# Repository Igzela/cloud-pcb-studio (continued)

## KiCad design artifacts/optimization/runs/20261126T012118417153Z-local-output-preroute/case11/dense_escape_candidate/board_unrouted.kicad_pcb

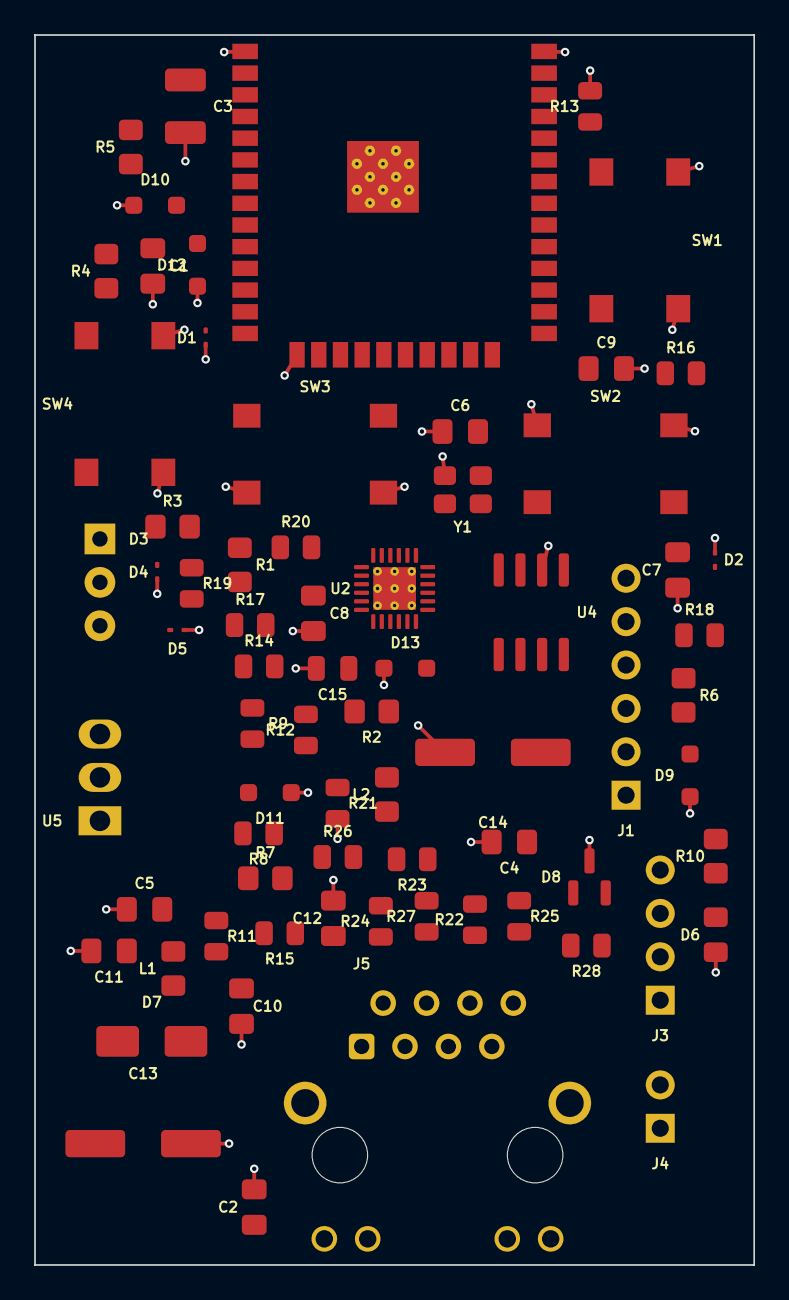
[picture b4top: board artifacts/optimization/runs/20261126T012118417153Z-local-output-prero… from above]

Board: 4 copper layers, 42.1 x 72.0 mm, 71 parts (0 on the bottom side), 49 nets.

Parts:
C1, C4: 1u; C_0805_2012Metric_Pad1.18x1.45mm_HandSolder
C2: 10u; C_0805_2012Metric_Pad1.18x1.45mm_HandSolder
C3: 100u; CP_EIA-3528-21_Kemet-B
C5, C7, C10, C11: 100n; C_0805_2012Metric_Pad1.18x1.45mm_HandSolder
C6, C8: 1uF; C_0805_2012Metric_Pad1.18x1.45mm_HandSolder
C9: 470pF; C_0805_2012Metric_Pad1.18x1.45mm_HandSolder
C12: 22nF; C_0805_2012Metric_Pad1.18x1.45mm_HandSolder
C13: 10uF; CP_Elec_6.3x4.9
C14: 1uF; CP_Elec_6.3x4.9
C15: 100nF; C_0805_2012Metric
D1, D2, D4, D5: ESD9B3; D_SOD-923
D3: LED_Dual_KAK; LED_D5.0mm-3
D6: LED; LED_0805_2012Metric_Pad1.15x1.40mm_HandSolder
D7: 1N5819; D_SMA
D8: NUP2105L; SOT-23
D9, D10, D11, D12, D13: PESD3V3L1BA; D_SOD-323_HandSoldering
J1: PROG; PinHeader_1x06_P2.54mm_Vertical
J3: Conn_Left_I2C; PinHeader_1x04_P2.54mm_Vertical
J4: Conn_01x02; PinHeader_1x02_P2.54mm_Vertical
J5: RJ45_Hanrun_HR911105A_Horizontal
L1, L2: BLM21SP181SN1D; R_0805_2012Metric_Pad1.20x1.40mm_HandSolder
R1, R2, R5, R6: 10k; R_0805_2012Metric_Pad1.20x1.40mm_HandSolder
R3, R4: 270R; R_0805_2012Metric_Pad1.20x1.40mm_HandSolder
R7: 0R; R_0805_2012Metric_Pad1.20x1.40mm_HandSolder
R8, R9: 10K; R_0805_2012Metric
R10: 470R; R_0805_2012Metric_Pad1.20x1.40mm_HandSolder
R11, R16, R18, R20: 33R; R_0805_2012Metric
R12: 1K5; R_0805_2012Metric
R13: 4K7; R_0805_2012Metric
R14, R15, R17, R19: 10R; R_0805_2012Metric
R21: 12K1; R_0805_2012Metric
R22, R23, R24, R27: 49R9; R_0805_2012Metric
R25, R26: 270R; R_0805_2012Metric
R28: 120R; R_0805_2012Metric
SW1: RESET; SW_SPST_Omron_B3FS-100xP
SW2: BOOT; SW_SPST_Omron_B3FS-100xP
SW3: Control 1; SW_SPST_Omron_B3FS-100xP
SW4: Control 2; SW_SPST_Omron_B3FS-100xP
U1: ESP32-WROOM-32
U2: LAN8720A; VQFN-24-1EP_4x4mm_P0.5mm_EP2.5x2.5mm_ThermalVias
U4: SN65HVD232; SOIC-8_3.9x4.9mm_P1.27mm
U5: R-78B3.3-2.0; Converter_DCDC_RECOM_R-78B-2.0_THT
Y1: 50MHz; Oscillator_SMD_Abracon_ASE-4Pin_3.2x2.5mm

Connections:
+3.3V: C2.1, C3.1, C6.2, C7.2, C8.1, C9.1, C14.1, C15.1, D13.2 (A2), J1.6, J5.9, J5.12, L1.2, L2.2, R1.2, R2.2, R5.2, R6.2, R7.2, R8.1, R9.1, R10.2, R11.1, R12.1, R15.1, U1.2 (VDD), U2.6 (VDDCR), U2.9 (VDDIO), U4.3 (VCC), U5.3 (OUT), Y1.4 (Vdd)
+24V: D7.2 (A), J3.1
/CAN/CANH: D8.2 (K), J3.2, J4.2, U4.7 (CANH)
/CAN/CANL: D8.1 (K), J3.3, R28.2, U4.6 (CANL)
/CPU/EN: C1.1, D1.2 (A2), D12.2 (A2), J1.5, R1.1, R5.1, SW1.2, U1.3 (EN)
/CPU/LEDA: R4.2, U1.6 (IO34)
/CPU/LEDB: R3.2, U1.7 (IO35)
/CPU/RX: J1.2, U1.34 (RXD0/IO3)
/CPU/TX: J1.3, U1.35 (TXD0/IO1)
/Ethernet/PHY_L1: R25.1, U2.3 (LED1/REGOFF)
/Ethernet/PHY_L2: R26.1, U2.2 (LED2/~INTSEL)
/Ethernet/PHY_RD+: J5.3 (RD+), R24.2, U2.23 (RXP)
/Ethernet/PHY_RD-: J5.6 (RD-), R27.2, U2.22 (RXN)
/Ethernet/PHY_TD+: J5.1 (TD+), R22.2, U2.21 (TXP)
/Ethernet/PHY_TD-: J5.2 (TD-), R23.2, U2.20 (TXN)
CTRL1: D4.2 (A2), D10.2 (A2), R8.2, SW3.1
CTRL2: D5.2 (A2), D11.2 (A2), R9.2, SW4.1
ETH_CRS_DV: R14.1, U1.12 (IO27)
ETH_EN_CLK: R13.1, U1.28 (IO17), Y1.1 (EN)
ETH_MDC: U1.37 (IO23), U2.13 (MDC)
ETH_MDIO: R12.2, U1.30 (IO18), U2.12 (MDIO)
ETH_RXCLK: C4.1, D2.2 (A2), D9.2 (A2), J1.4, R2.1, R6.1, R16.1, R18.1, SW2.2, U1.25 (IO0)
ETH_RXD0: R19.1, U1.10 (IO25)
ETH_RXD1: R17.1, U1.11 (IO26)
ETH_TXD0: U1.31 (IO19), U2.17 (TXD0)
ETH_TXD1: U1.36 (IO22), U2.18 (TXD1)
ETH_TXEN: U1.33 (IO21), U2.16 (TXEN)
GND: C1.2, C2.2, C3.2, C4.2, C5.1, C6.1, C7.1, C8.2, C9.2, C10.2, C11.2, C12.2, C13.2, C14.2, C15.2, D1.1 (A1), D2.1 (A1), D4.1 (A1), D5.1 (A1), D6.1 (K), D8.3 (A), D9.1 (A1), D10.1 (A1), D11.1 (A1), D12.1 (A1), D13.1 (A1), J1.1, J3.4, J5.8, J5.SH, R13.2, R21.2, SW1.1, SW2.1, SW3.2, SW4.2, U1.1 (GND), U1.15 (GND), U1.38 (GND), U1.39 (GND), U2.25 (VSS), U4.2 (GND), U5.2 (GND), Y1.2 (GND)
unnamed: D3.2 (A), R7.1
unnamed: D3.1 (K1), R4.1
unnamed: D3.3 (K2), R3.1
unnamed: D6.2 (A), R10.1
unnamed: C13.1, D7.1 (K), U5.1 (IN)
unnamed: J4.1, R28.1
unnamed: J5.10, R26.2
unnamed: J5.11, R25.2
unnamed: C12.1, J5.4 (TCT), J5.5 (RCT), L2.1, R22.1, R23.1, R24.1, R27.1
unnamed: R14.2, U2.11 (CRS_DV/MODE2)
unnamed: R21.1, U2.24 (RBIAS)
unnamed: R19.2, U2.8 (RXD0/MODE0)
unnamed: R17.2, U2.7 (RXD1/MODE1)
unnamed: R15.2, U2.10 (RXER/PHYAD0)
unnamed: C10.1, C11.1, L1.1, U2.1 (VDD2A), U2.19 (VDD1A)
unnamed: R20.1, U2.5 (XTAL1/CLKIN)
unnamed: R18.2, U2.14 (~INT/REFCLKO)
unnamed: R16.2, R20.2, Y1.3 (OUT)
PHY_RST: C5.2, R11.2, U2.15 (~RST)
RXCAN: U1.18 (SWP/SD3), U4.4 (R)
TXCAN: U1.17 (SHD/SD2), U4.1 (D)

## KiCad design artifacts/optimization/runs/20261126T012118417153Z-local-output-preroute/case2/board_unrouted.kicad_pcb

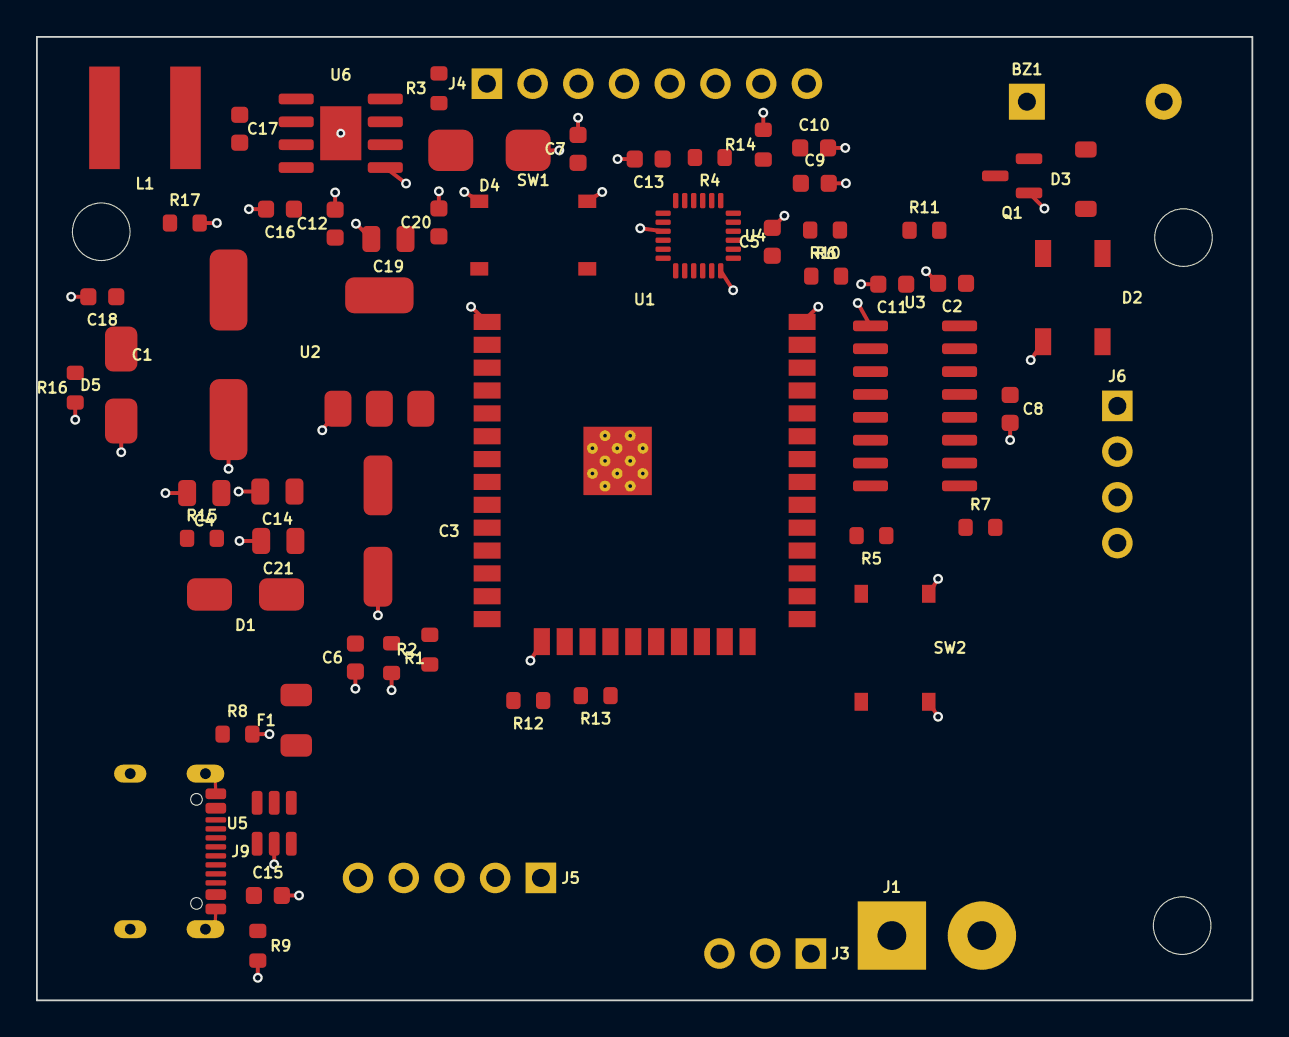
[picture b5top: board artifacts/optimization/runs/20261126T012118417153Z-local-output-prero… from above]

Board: 4 copper layers, 67.5 x 53.5 mm, 64 parts (0 on the bottom side), 50 nets.

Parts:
BZ1: Buzzer; Buzzer_12x9.5RM7.6
C1: 100uF 35V; C_Elec_8x10.2
C2, C5, C6, C7, C8, C9, C12, C13, C15, C16, C17, C20: 100nF; C_0603_1608Metric
C3: 100uF 16V; C_Elec_6.3x5.8
C4: 10uF 16V; C_0805_2012Metric
C10: 2.2nF; C_0603_1608Metric
C11: 10nF; C_0603_1608Metric
C14: 22uF; C_0805_2012Metric
C18: 220p; C_0603_1608Metric
C19, C21: 10uF; C_0805_2012Metric
D1: SS34; D_SMA
D2: WS2812B; LED_WS2812B_PLCC4_5.0x5.0mm_P3.2mm
D3: 1N4148; D_SOD-123
D4: SM6T24A; D_SMB
D5: D_Schottky; D_SMA
F1: 500mA; Fuse_1206_3216Metric
H1, H2, H3: M_3.2mm; MountingHole_3.2mm
J1: Battery XT30; AMASS_XT30U-M_1x02_P5.0mm_Vertical
J3: IBUS/SBUS RECIEVER; PinHeader_1x03_P2.54mm_Vertical
J4: PWM RECIEVER; PinHeader_1x08_P2.54mm_Vertical
J5: MOTOR OUT; PinHeader_1x05_P2.54mm_Vertical
J6: GPS; PinHeader_1x04_P2.54mm_Vertical
J9: USB_C_Receptacle_USB2.0_16P; USB_C_Receptacle_GCT_USB4105-xx-A_16P_TopMnt_Horizontal
L1: 22u; L_Sunlord_SWPA6028S
Q1: 2N3904; SOT-23
R1: 22k; R_0603_1608Metric
R2, R3: 100k; R_0603_1608Metric
R4, R5: 10k; R_0603_1608Metric
R6: 1k; R_0603_1608Metric
R7: 330k; R_0603_1608Metric
R8, R9: 5.1k; R_0603_1608Metric
R10, R11: 4.7k; R_0603_1608Metric
R12, R13: 22; R_0603_1608Metric
R14: 200k; R_0603_1608Metric
R15: 211k; R_0603_1608Metric
R16: 40.2k; R_0603_1608Metric
R17: 68.1k; R_0603_1608Metric
SW1: RESET; SW_Push_1P1T_XKB_TS-1187A
SW2: BOOT; SW_Push_1P1T_XKB_TS-1187A
U1: ESP32-WROOM-32E; ESP32-WROOM-32D
U2: AMS1117-3.3; SOT-223-3_TabPin2
U3: CH340C; SOIC-16_3.9x9.9mm_P1.27mm
U4: MPU-6050; InvenSense_QFN-24_4x4mm_P0.5mm
U5: USBLC6-2SC6; SOT-23-6
U6: MP1584EN; SOIC-8-1EP_3.9x4.9mm_P1.27mm_EP2.29x3mm

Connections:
+3.3V: C2.1, C4.1, C5.1, C7.1, C11.1, C12.1, C13.1, J6.1, R4.1, R5.1, R10.1, R11.1, U1.2, U2.2, U3.16, U4.8, U4.13
+3V3: BZ1.2, D2.1, D3.1
+5V: C3.1, C14.1, C19.1, C20.1, C21.1, F1.2, J3.2, J4.7, L1.1, R15.2, U2.3
+BATT: D1.2, J1.1, R2.1
/VIN: C1.2, C16.1, D1.1, D4.2, R3.1, U6.7
/usb+: J9.A6, J9.B6, U5.1
/usb-: J9.A7, J9.B7, U5.3
/usb_esd-: R13.2, U5.4
/usb_mcu+: R12.1, U3.5
/usb_mcu-: R13.1, U3.6
BUZZER: R6.1, U1.16
CH1: J4.1, U1.8
CH2: J4.2, U1.9
CH3: J4.3, U1.7
CH4: J4.4, U1.30
CH5: J4.5, U1.31
CH6: J4.6, U1.37
ESC1: J5.1, U1.10
ESC2: J5.2, U1.11
ESC3: J5.3, U1.12
ESC4: J5.4, U1.13
GND: C1.1, C2.2, C3.2, C4.2, C5.2, C6.1, C7.2, C8.2, C9.2, C10.2, C11.2, C12.2, C13.2, C14.2, C15.2, C16.2, C18.2, C19.2, C20.2, C21.2, D2.3, D4.1, D5.1, J1.2, J3.3, J4.8, J5.5, J6.2, J9.A1, J9.A12, J9.B1, J9.B12, J9.S1, Q1.1, R1.2, R8.2, R9.2, R14.2, R16.1, R17.2, SW1.1, SW2.1, U1.1, U1.15, U1.38, U1.39, U2.1, U3.1, U4.9, U4.11, U4.18, U5.2, U6.5, U6.9
GPS RX: J6.4, U1.28
GPS TX: J6.3, U1.29
INT: U1.6, U4.12
LED_STAT: R7.1, U1.26
unnamed: BZ1.1, D3.2, Q1.2
unnamed: D2.4, R7.2
unnamed: C17.2, D5.2, L1.2, U6.1
unnamed: J9.A5, R8.1
unnamed: J9.B5, R9.1
unnamed: Q1.3, R6.2
unnamed: R12.2, U5.6
unnamed: R4.2, SW1.2, U1.3
unnamed: R5.2, SW2.2, U1.25
unnamed: C8.1, U3.4
unnamed: C10.1, U4.20
unnamed: C9.1, U4.10
unnamed: C15.1, F1.1, J9.A4, J9.A9, J9.B4, J9.B9, U5.5
unnamed: C17.1, U6.8
unnamed: C18.1, R17.1, U6.3
unnamed: R3.2, U6.2
unnamed: R15.1, R16.2, U6.4
unnamed: R14.1, U6.6
RX: U1.34, U3.2
SCL: R11.2, U1.36, U4.23
SDA: R10.2, U1.33, U4.24
SENOR_VP: C6.2, R1.1, R2.2, U1.4
TX: U1.35, U3.3
iBUS/SBUS RX: J3.1, U1.27

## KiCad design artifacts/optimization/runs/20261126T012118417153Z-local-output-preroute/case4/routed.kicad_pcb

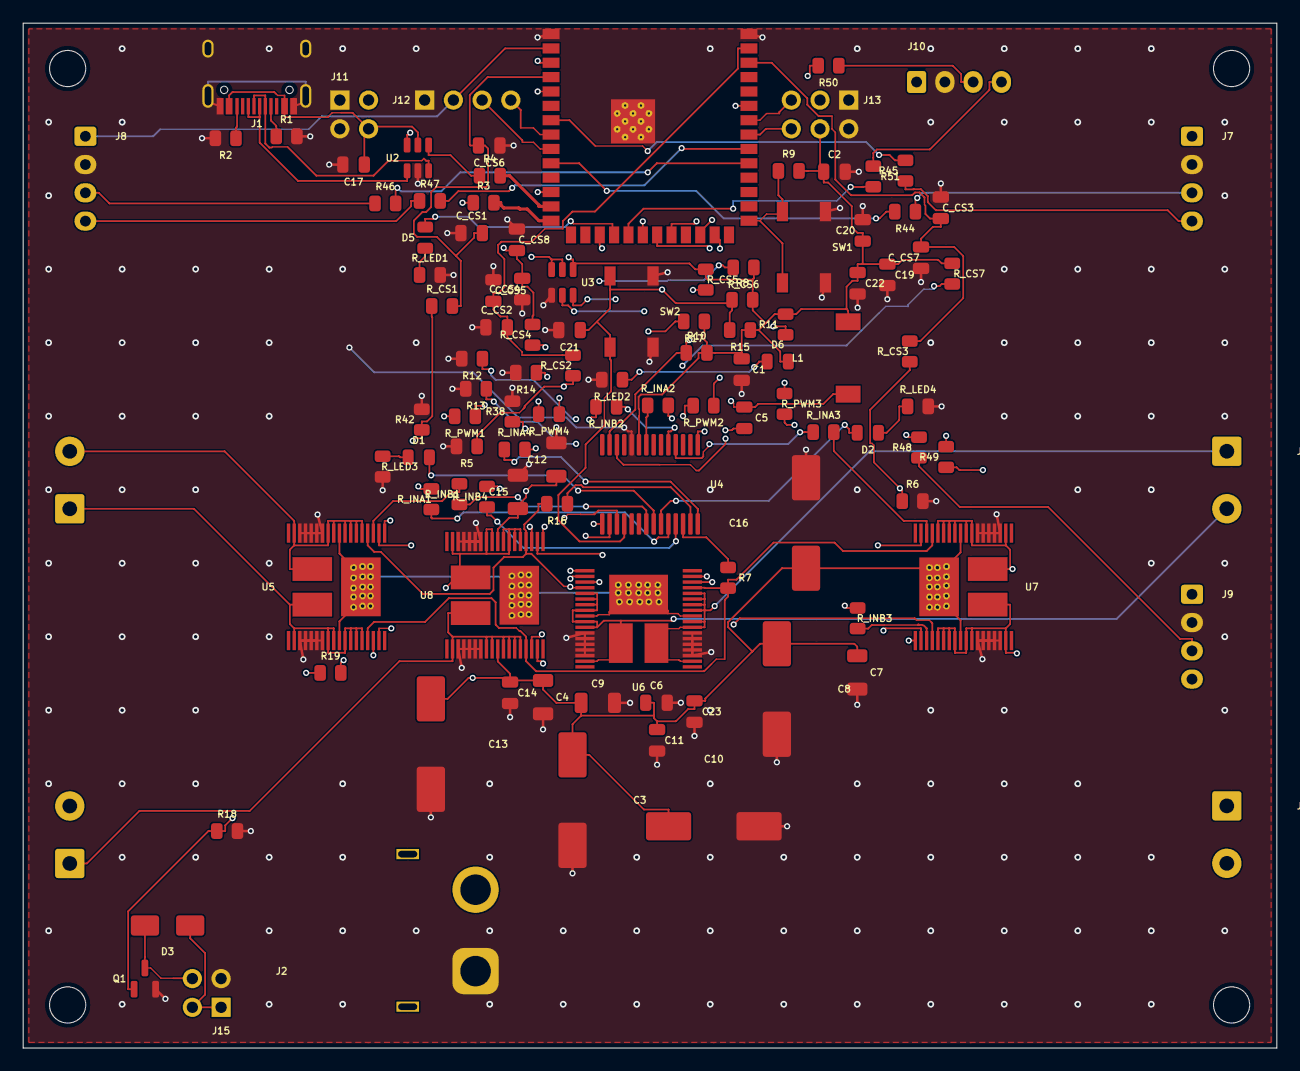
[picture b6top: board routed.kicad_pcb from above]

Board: 4 copper layers, 110.8 x 90.6 mm, 117 parts (0 on the bottom side), 98 nets.

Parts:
C1, C2: 22uF; C_0805_2012Metric
C3, C8, C10, C13, C16: 470uF; CP_Elec_10x10
C4, C7, C9, C12, C15: 10uF; C_1206_3216Metric
C5, C6, C11, C14, C19, C21, C22, C23: 100nF; C_0805_2012Metric
C17, C20: 10uF; C_0805_2012Metric
C_CS1, C_CS2, C_CS3, C_CS4: 100nF; C_0805_2012Metric
C_CS5, C_CS6, C_CS7, C_CS8: 10uF; C_0805_2012Metric
D1: Red LED; LED_0805_2012Metric
D2: Green LED; LED_0805_2012Metric
D3: D_Schottky; D_SMA
D5: Blue LED; LED_0805_2012Metric
D6: Orange LED; LED_0805_2012Metric
H1, H2, H3, H4: M_3.2mm; MountingHole_3.2mm
J1: USB_C_Receptacle_USB2.0_16P; USB_C_Receptacle_HRO_TYPE-C-31-M-12
J2: Conn_01x02; AMASS_XT60PW-M_1x02_P7.20mm_Horizontal
J3, J4, J5, J6: Conn_01x02; TerminalBlock_Phoenix_MKDS-3-2-5.08_1x02_P5.08mm_Horizontal
J7, J8, J9, J10: Conn_01x04; JST_XH_B4B-XH-A_1x04_P2.50mm_Vertical
J11: 5v breakout; PinHeader_2x02_P2.54mm_Vertical
J12: I2C sda scl; PinHeader_1x04_P2.54mm_Vertical
J13: 41(40)_3v3_gnd; PinHeader_2x03_P2.54mm_Vertical
J15: IN OUT; PinHeader_2x02_P2.54mm_Vertical
L1: 4.7uH; L_7.3x7.3_H4.5
Q1: Q_NMOS_GDS; SOT-23
R1, R2: 5.1K; R_0805_2012Metric
R3, R4: 27R; R_0805_2012Metric
R5, R6, R17, R38, R42: 1K; R_0805_2012Metric
R7, R16: 1k; R_0805_2012Metric
R8, R9, R12, R13, R14, R15: 10K; R_0805_2012Metric
R10, R11: 4.7K; R_0805_2012Metric
R18: 10k; R_0805_2012Metric
R19, R44, R45, R46, R47, R48, R49, R50, R51: 100R; R_0805_2012Metric
R_CS1, R_CS2, R_CS3, R_CS4, R_CS5, R_CS6, R_CS7: 1k; R_0805_2012Metric
R_INA1, R_INA2, R_INA3, R_INA4: 1K; R_0805_2012Metric
R_INB1, R_INB2, R_INB3, R_INB4: 1K; R_0805_2012Metric
R_LED1, R_LED2, R_LED3, R_LED4: 330R; R_0805_2012Metric
R_PWM1, R_PWM2, R_PWM3, R_PWM4: 1K; R_0805_2012Metric
SW1: SW_Boot; SW_SPST_TL3342
SW2: SW_RESET; SW_SPST_TL3342
U1: ESP32-S3-WROOM-1
U2: USBLC6-2SC6; SOT-23-6
U3: AP63203WU-7; TSOT-23-6-AP63203WU
U4: MCP23017_SS; SSOP-28_5.3x10.2mm_P0.65mm
U5, U6, U7, U8: VNH7040AYTR; POWERSSO-36TP_STM_jr

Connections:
/3V3: C1.1, C2.1, C19.1, C20.1, C22.1, D6.2 (A), J7.1, J8.1, J9.1, J10.1, J12.2, J13.3, J13.4, L1.2, R8.2, R9.2, R10.2, R11.2, R15.1, R17.1, R_CS5.1, R_CS6.1, R_CS7.1, U1.2 (3V3), U3.1 (FB), U4.9 (VDD)
/3V3_M1: R_CS6.2, U5.20
/3V3_M2: R_CS7.2, U6.20
/3V3_m3: R_CS5.2, U7.20
/3v3_light: R17.2, U8.20
/5V_USB: C17.1, J1.A4 (VBUS), J1.A9 (VBUS), J1.B4 (VBUS), J1.B9 (VBUS), J11.2, J11.4, U2.5 (VBUS), U3.2 (EN), U3.3 (IN)
/ENCA_M1: R44.2, U1.10 (IO17)
/ENCA_M2: R46.2, U1.31 (IO38)
/ENCA_M3: R48.2, U1.22 (IO14)
/ENCA_M4: R50.2, U1.20 (IO12)
/ENCB_M1: R45.2, U1.7 (IO7)
/ENCB_M2: R47.2, U1.32 (IO39)
/ENCB_M3: R49.2, U1.24 (IO47)
/ENCB_M4: R51.2, U1.19 (IO11)
/ESP_EN: C21.1, R8.1, R15.2, SW2.2, U1.3 (EN), U4.18 (~RESET)
/GPIO40: J13.6, U1.33 (IO40)
/GPIO41: J13.5, U1.34 (IO41)
/Green_LED: D2.2 (A), U4.23 (GPA2)
/I2C_SCL: J12.4, R11.1, U1.8 (IO15), U4.12 (SCK)
/I2C_SDA: J12.3, R10.1, U1.9 (IO16), U4.13 (SDA)
/LED_ESP32: D5.2 (A), U1.18 (IO10)
/M1_CS: R42.1, R_CS1.1, U5.19
/M1_CS_ADC: C_CS1.2, C_CS6.2, R_CS1.2, U1.4 (IO4)
/M1_INA: R_INA1.2, U5.16
/M1_INA_ESP32: R_INA1.1, U4.24 (GPA3)
/M1_INB: R_INB1.2, U5.21
/M1_INB_ESP32: R_INB1.1, U4.21 (GPA0)
/M1_OUTA: J3.1, U5.2, U5.8, U5.9, U5.11, U5.12, U5.13, U5.14, U5.38
/M1_OUTB: J3.2, U5.23, U5.24, U5.25, U5.26, U5.28, U5.29, U5.35, U5.39
/M1_PWM: R_PWM1.2, U5.17
/M1_PWM_ESP: R_PWM1.1, U1.12 (IO8)
/M2_CS: R5.1, R_CS2.1, U6.19
/M2_CS_ADC: C_CS2.2, C_CS5.2, R_CS2.2, U1.39 (IO1)
/M2_INA: R_INA2.2, U6.16
/M2_INA_ESP32: R_INA2.1, U4.8 (GPB7)
/M2_INB: R_INB2.2, U6.21
/M2_INB_ESP32: R_INB2.1, U4.5 (GPB4)
/M2_OUTA: J4.1, U6.2, U6.8, U6.9, U6.11, U6.12, U6.13, U6.14, U6.38
/M2_OUTB: J4.2, U6.23, U6.24, U6.25, U6.26, U6.28, U6.29, U6.35, U6.39
/M2_PWM: R_PWM2.2, U6.17
/M2_PWM_ESP: R_PWM2.1, U1.25 (IO48)
/M3_CS: R6.1, R_CS3.1, U7.19
/M3_CS_ADC: C_CS3.2, C_CS7.2, R_CS3.2, U1.38 (IO2)
/M3_INA: R_INA3.2, U7.16
/M3_INA_ESP32: R_INA3.1, U4.4 (GPB3)
/M3_INB: R_INB3.2, U7.21
/M3_INB_ESP32: R_INB3.1, U4.1 (GPB0)
/M3_OUTA: J5.1, U7.2, U7.8, U7.9, U7.11, U7.12, U7.13, U7.14, U7.38
/M3_OUTB: J5.2, U7.23, U7.24, U7.25, U7.26, U7.28, U7.29, U7.35, U7.39
/M3_PWM: R_PWM3.2, U7.17
/M3_PWM_ESP: R_PWM3.1, U1.21 (IO13)
/M4_CS: R38.1, R_CS4.1, U8.19
/M4_CS_ADC: C_CS4.2, C_CS8.2, R_CS4.2, U1.5 (IO5)
/M4_INA: R_INA4.2, U8.16
/M4_INA_ESP32: R_INA4.1, U4.28 (GPA7)
/M4_INB: R_INB4.2, U8.21
/M4_INB_ESP32: R_INB4.1, U4.25 (GPA4)
/M4_OUTA: J6.1, U8.2, U8.8, U8.9, U8.11, U8.12, U8.13, U8.14, U8.38
/M4_OUTB: J6.2, U8.23, U8.24, U8.25, U8.26, U8.28, U8.29, U8.35, U8.39
/M4_PWM: R_PWM4.2, U8.17
/M4_PWM_ESP: R_PWM4.1, U1.17 (IO9)
/Red_LED: D1.2 (A), U4.22 (GPA1)
/SEL_0: R7.2, U5.15, U6.15, U7.15, U8.15
/SEL_0_CTRL: R7.1, U4.26 (GPA5)
/SEL_1: R16.2, U5.22, U6.22, U7.22, U8.22
/SEL_1_CTRL: R16.1, U4.27 (GPA6)
/USB_D+: R3.2, U1.14 (USB_D+)
/USB_D-: R4.2, U1.13 (USB_D-)
/VMOT: C3.1, C4.1, C6.1, C7.1, C8.1, C9.1, C10.1, C11.1, C12.1, C13.1, C14.1, C15.1, C16.1, C23.1, J2.2, U5.10, U5.27, U5.37, U6.10, U6.27, U6.37, U7.10, U7.27, U7.37, U8.10, U8.27, U8.37
GND: C1.2, C2.2, C3.2, C4.2, C6.2, C7.2, C8.2, C9.2, C10.2, C11.2, C12.2, C13.2, C14.2, C15.2, C16.2, C17.2, C19.2, C20.2, C21.2, C22.2, C23.2, C_CS1.1, C_CS2.1, C_CS3.1, C_CS4.1, C_CS5.1, C_CS6.1, C_CS7.1, C_CS8.1, J1.A1 (GND), J1.A12 (GND), J1.B1 (GND), J1.B12 (GND), J1.S1 (SHIELD), J2.1, J7.2, J8.2, J9.2, J10.2, J11.1, J11.3, J12.1, J13.1, J13.2, J15.3, Q1.2 (S), R1.2, R2.2, R5.2, R6.2, R12.2, R13.2, R14.2, R18.2, R38.2, R42.2, R_LED1.2, R_LED2.2, R_LED3.2, R_LED4.2, SW1.1, SW2.1, U1.1 (GND), U1.40 (GND), U1.41 (GND), U2.2 (GND), U3.4 (GND), U4.10 (VSS), U5.3, U5.4, U5.5, U5.6, U5.7, U5.30, U5.31, U5.32, U5.33, U5.34, U6.3, U6.4, U6.5, U6.6, U6.7, U6.30, U6.31, U6.32, U6.33, U6.34, U7.3, U7.4, U7.5, U7.6, U7.7, U7.30, U7.31, U7.32, U7.33, U7.34, U8.3, U8.4, U8.5, U8.6, U8.7, U8.30, U8.31, U8.32, U8.33, U8.34
unnamed: D1.1 (K), R_LED3.1
unnamed: D2.1 (K), R_LED4.1
unnamed: D3.2 (A), J15.4, Q1.3 (D)
unnamed: D3.1 (K), J15.1, J15.2
unnamed: D5.1 (K), R_LED1.1
unnamed: D6.1 (K), R_LED2.1
unnamed: J1.A5 (CC1), R1.1
unnamed: J1.B5 (CC2), R2.1
unnamed: J1.A6 (D+), J1.B6 (D+), U2.1 (I/O1)
unnamed: J1.A7 (D-), J1.B7 (D-), U2.3 (I/O2)
unnamed: J7.3, R44.1
unnamed: J7.4, R45.1
unnamed: J8.3, R46.1
unnamed: J8.4, R47.1
unnamed: J9.3, R48.1
unnamed: J9.4, R49.1
unnamed: J10.3, R50.1
unnamed: J10.4, R51.1
unnamed: Q1.1 (G), R18.1, R19.1
unnamed: R3.1, U2.6 (I/O1)
unnamed: R4.1, U2.4 (I/O2)
unnamed: R9.1, SW1.2, U1.27 (IO0)
unnamed: R19.2, U1.35 (IO42)
unnamed: C5.2, U3.6 (BST)
unnamed: C5.1, L1.1, U3.5 (SW)
unnamed: R12.1, U4.15 (A0)
unnamed: R13.1, U4.16 (A1)
unnamed: R14.1, U4.17 (A2)

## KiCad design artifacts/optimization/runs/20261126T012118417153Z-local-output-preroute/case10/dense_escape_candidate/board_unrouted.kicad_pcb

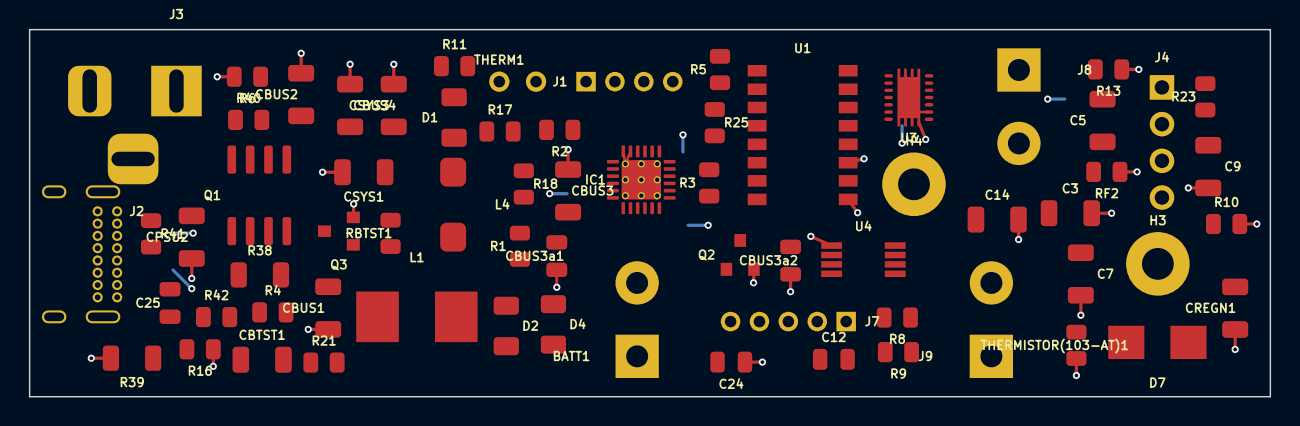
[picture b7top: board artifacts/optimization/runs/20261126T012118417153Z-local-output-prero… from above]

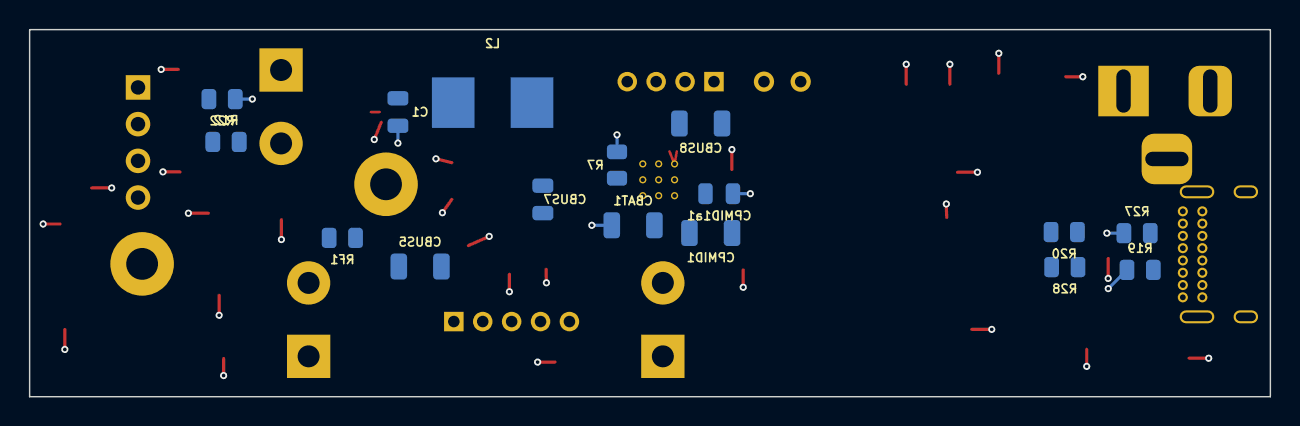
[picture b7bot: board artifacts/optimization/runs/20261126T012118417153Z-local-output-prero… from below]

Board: 4 copper layers, 85.9 x 25.4 mm, 84 parts (16 on the bottom side), 50 nets.

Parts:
BATT1: 1s LiPo; TerminalBlock_bornier-2_P5.08mm
C1, C24: 0.1uF; C_0805_2012Metric
C3, C5, C7, C9, C14: 22uF; C_1206_3216Metric
C12: 4.7pF; C_0805_2012Metric
C25: 1nF; C_0805_2012Metric
CBAT1: 10uF; C_1206_3216Metric
CBTST1: 1uF; C_1206_3216Metric
CBUS1, CBUS4: 10uF; C_1206_3216Metric
CBUS2, CBUS3, CBUS5, CBUS8: 1uF; C_1206_3216Metric
CBUS3a1, CBUS3a2, CBUS7: 0.1uF; C_0805_2012Metric
CPMID1: 10uF; C_1206_3216Metric
CPMID1a1: 0.1uF; C_0805_2012Metric
CPSU2: 1uF; C_1206_3216Metric
CREGN1: 1uF; C_1206_3216Metric
CSYS1, CSYS3: 10uF; C_1206_3216Metric
D1, D2, D4: Led; LED_1206_3216Metric
D7: B320; D_SMB
H3: hole; MountingHole_2.2mm_M2_Pad
H4: MountingHole_Pad; MountingHole_2.2mm_M2_Pad
IC1: BQ24193; QFN-24-1EP_4x4mm_P0.5mm_EP2.7x2.7mm_ThermalVias
J1: AudioIN; PinSocket_1x04_P2.00mm_Vertical
J2: USB_C_Receptacle_USB2.0; USB_C_Receptacle_GCT_USB4085
J3: 5-15V / 3-5A; BarrelJack_Horizontal
J4: AudioOUT; PinSocket_1x04_P2.54mm_Vertical
J7: uC host; PinSocket_1x05_P2.00mm_Vertical
J8: 5V 3A; TerminalBlock_bornier-2_P5.08mm
J9: 12V 2A; TerminalBlock_bornier-2_P5.08mm
L1: 2.2uH 4A; L_Bourns_SRP7028A_7.3x6.6mm
L2: 1.5uH 4A; L_Bourns_SRP7028A_7.3x6.6mm
L4: 4.7uH 2A; L_Bourns_SRP5030T
Q1: IRF7404; SOIC-8_3.9x4.9mm_P1.27mm
Q2, Q3: BSS138; SOT-23
R1, R2, R3, R6, R16, R17, R18, R42: 10K; R_0805_2012Metric
R4, R5, R8, R9, R11, R21: 2K2; R_0805_2012Metric
R7: 265; R_0805_2012Metric
R10: 6K8; R_0805_2012Metric
R12, R23: 1M; R_0805_2012Metric
R13: 180K; R_0805_2012Metric
R19, R27: 5K1; R_0805_2012Metric
R20, R28: 56K; R_0805_2012Metric
R22: 270K; R_0805_2012Metric
R25: 150K; R_0805_2012Metric
R38: 120K; R_1206_3216Metric
R39: 49K9; R_1206_3216Metric
R40: 262K; R_0805_2012Metric
R41: 100K; R_0805_2012Metric
RBTST1: R; R_0805_2012Metric
RF1: 820K; R_0805_2012Metric
RF2: 100K; R_0805_2012Metric
THERM1: thermistor; TestPoint_2Pads_Pitch2.54mm_Drill0.8mm
THERMISTOR(103-AT)1: 10K; R_0805_2012Metric
U1: PAM8403-SOP16; SOP-16_4.4x10.4mm_P1.27mm
U3: TPS63020; QFN14-3X4MM
U4: LM2623; VSSOP-8_3.0x3.0mm_P0.65mm

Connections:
5V: C3.1, C5.1, C7.1, C9.1, CBUS3a2.2, J8.2, R12.2, R23.2, U3.4 (VOUT), U3.5 (VOUT_2)
12V: C14.1, D7.1 (K), J9.2, RF1.2, U4.2 (EN), U4.6 (VDD), U4.7 (BOOT)
/CE: IC1.9 (/CE), J7.5, R6.1
/D+: IC1.2 (PSEL), J2.A6 (D+), J2.B6 (D+), R16.2
/D-: IC1.3 (/PG), J2.A7 (D-), J2.B7 (D-), R4.1
/INT: IC1.7 (INT), J7.4, R1.1
/OTG: IC1.8 (OTG), Q2.3 (D), R17.1
/SCL: IC1.5 (SCL), J7.2, R3.1
/SDA: IC1.6 (SDA), J7.3, R2.1
unnamed: BATT1.2, CBAT1.2, IC1.13 (BAT), IC1.14 (BAT)
unnamed: CBTST1.1, RBTST1.1
unnamed: CBUS5.1, R9.1
unnamed: CBUS8.1, R11.1
unnamed: D1.2 (C), R4.2
unnamed: D2.2 (C), R5.2
unnamed: D4.2 (C), R21.1
unnamed: C12.2, D7.2 (A), L4.2, U4.8 (SW)
unnamed: CBTST1.2, IC1.21 (BTST)
unnamed: IC1.10 (ILIM), R7.1
unnamed: CREGN1.2, IC1.22 (REGN), R8.1
unnamed: IC1.4 (STAT), R5.1
unnamed: IC1.19 (SW), IC1.20 (SW), L1.1, RBTST1.2
unnamed: IC1.11 (TS1), IC1.12 (TS2), R8.2, R10.1, THERM1.2, THERMISTOR(103-AT)1.2
unnamed: J1.1, R9.2
unnamed: J1.3, R11.2
unnamed: J1.4, R18.2, U1.5 (MUTE_LOW)
unnamed: J2.A5 (CC1), R20.1, R27.2
unnamed: J2.B5 (CC2), R19.2, R28.1
unnamed: J4.1, U1.3 (-OUT_L)
unnamed: J4.2, U1.1 (+OUT_L)
unnamed: J4.3, U1.16 (+OUT_R)
unnamed: J4.4, U1.14 (-OUT_R)
unnamed: C25.1, Q1.4 (G), Q3.3 (D), R42.2
unnamed: Q2.1 (G), R38.2, R39.1
unnamed: Q3.1 (G), R40.2, R41.1
unnamed: CBUS8.2, U1.7 (IN_L)
unnamed: CBUS5.2, U1.10 (IN_R)
unnamed: CBUS7.2, U1.8 (VREF)
unnamed: C1.1, U3.1 (VINA), U3.12 (EN), U3.13 (PS/SYNC)
unnamed: R12.1, R13.2, R22.2, U3.3 (FB)
unnamed: L2.1, U3.8 (L1), U3.9 (L1_2)
unnamed: L2.2, U3.6 (L2), U3.7 (L2_2)
unnamed: R21.2, R23.1, U3.14 (PG)
unnamed: RF1.1, RF2.2, U4.4 (FB)
unnamed: C12.1, R25.1, U4.3 (FREQ)
PGND: BATT1.1, C1.2, C3.2, C5.2, C7.2, C9.2, C14.2, C24.1, CBAT1.1, CBUS1.1, CBUS2.2, CBUS3.1, CBUS3a1.1, CBUS3a2.1, CBUS4.1, CBUS7.1, CPMID1.1, CPMID1a1.1, CPSU2.1, CREGN1.1, CSYS1.2, CSYS3.2, H3.1, H4.1, IC1.17 (PGND), IC1.18 (PGND), IC1.25 (PGND), J1.2, J2.A1 (GND), J2.A12 (GND), J2.B1 (GND), J2.B12 (GND), J2.S1 (SHIELD), J3.2, J7.1, J8.1, J9.1, Q2.2 (S), Q3.2 (S), R6.2, R7.2, R10.2, R13.1, R16.1, R19.1, R22.1, R27.1, R39.2, R41.2, RF2.1, THERM1.1, THERMISTOR(103-AT)1.1, U1.2 (PGND), U1.9 (NC), U1.11 (GND), U1.15 (PGND), U3.2 (GND), U3.15 (PGND), U3.16 (PGND1), U3.17 (PGND2), U3.18 (PGND3), U3.19 (PGND4), U3.20 (PGND5), U3.21 (PGND6), U3.22 (PGND7), U3.23 (PGND8), U4.1 (PGND), U4.5 (SGND)
POWERBANKOUT: CPMID1.2, CPMID1a1.2, IC1.23 (PMID)
VBUS: C25.2, CBUS3.2, CBUS3a1.2, CPSU2.2, IC1.1 (VBUS), IC1.24 (VBUS), J2.A4 (VBUS), J2.A9 (VBUS), J2.B4 (VBUS), J2.B9 (VBUS), Q1.1 (S), Q1.2 (S), Q1.3 (S), R20.2, R28.2, R42.1
VPSU: J3.1, Q1.5 (D), Q1.6 (D), Q1.7 (D), Q1.8 (D), R38.1, R40.1
VSYS: C24.2, CBUS1.2, CBUS2.1, CBUS4.2, CSYS1.1, CSYS3.1, D1.1 (A), D2.1 (A), D4.1 (A), IC1.15 (SYS), IC1.16 (SYS), L1.2, L4.1, R1.2, R2.2, R3.2, R17.2, R18.1, R25.2, U1.4 (PVDD), U1.6 (VDD), U1.12 (SHDN_LOW), U1.13 (PVDD), U3.10 (VIN), U3.11 (VIN_2)
